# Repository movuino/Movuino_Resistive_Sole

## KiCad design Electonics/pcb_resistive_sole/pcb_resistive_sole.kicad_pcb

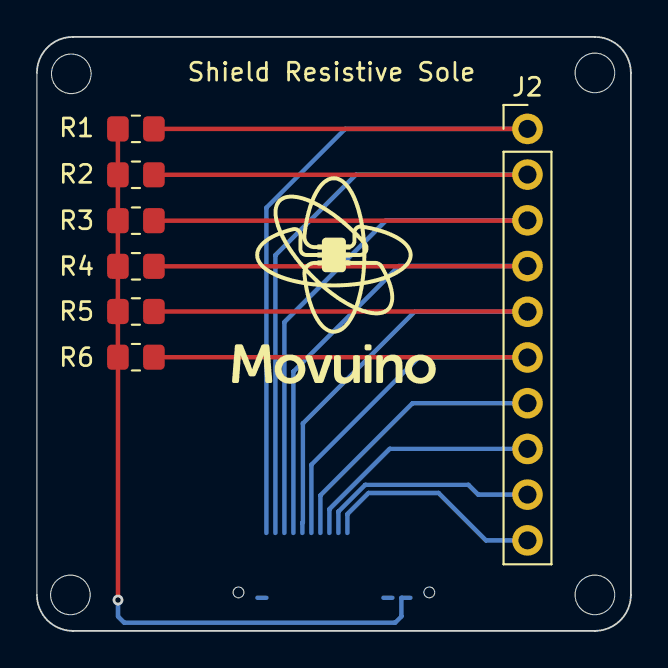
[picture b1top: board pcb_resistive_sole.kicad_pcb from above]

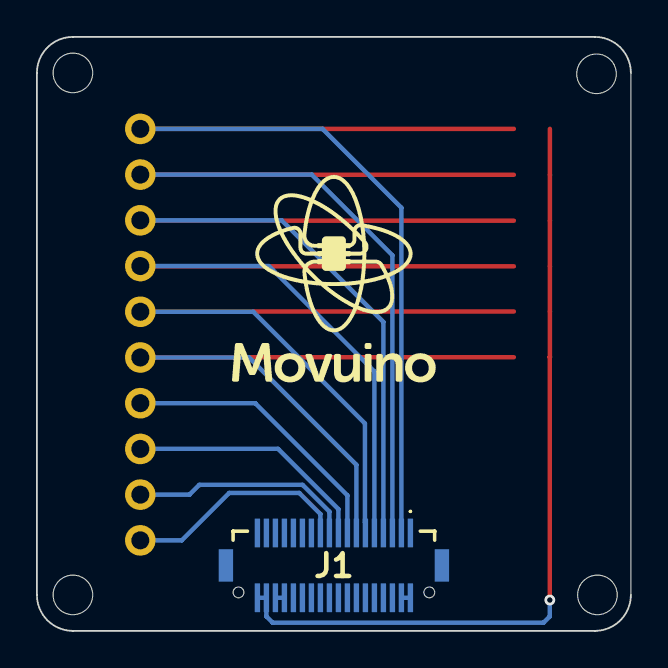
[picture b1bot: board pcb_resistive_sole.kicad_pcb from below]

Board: 2 copper layers, 33.0 x 33.0 mm, 10 parts (2 on the bottom side), 13 nets.

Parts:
J1: DF12_3.0_-36DP-0.5V_86_; DF123036DP05V86
J2: Conn_01x10; PinHeader_1x10_P2.54mm_Vertical
R1, R2, R3, R4, R5, R6: 10k; R_0805_2012Metric_Pad1.20x1.40mm_HandSolder
U$8, U$8#2: LOGO_MOVUINOBOTTOM_11MM; LOGO_MOVUINO_BMP_11MM-BOTTOM

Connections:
/3v3: J1.30, J1.32
/5V: J1.2, J1.4
/GND: J1.34, J1.36, R1.2, R2.2, R3.2, R4.2, R5.2, R6.2
/IO25: J1.17, J2.8
/IO26: J1.19, J2.9
/IO27: J1.21, J2.10
/IO32: J1.13, J2.6, R6.1
/IO33: J1.15, J2.7
/IO34: J1.7, J2.3, R3.1
/IO35: J1.11, J2.5, R5.1
/IO37: J1.9, J2.4, R4.1
/IO38: J1.3, J2.1, R1.1
/IO39: J1.5, J2.2, R2.1

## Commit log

2022-10-24 dry firmware
2022-10-24 dry processing
2023-10-11 init
2023-10-11 fixed
